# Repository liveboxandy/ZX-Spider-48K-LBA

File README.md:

# ZX-Spider-48K-LBA
ZX Spider 48K Amended by liveboxandy to use 9 Pin MiniDIN and move resistors from under IC's.

Original files from https://github.com/konkotgit/ZX-48-Spider and redrawn in Kicad 10 using the gerbers from konkotgit as an initial layout.
Autorouting along with some manual actions were used for the final pcb layout and gerber generation.

See https://github.com/konkotgit/ZX-48-Spider for more details and any issues that might be seen.

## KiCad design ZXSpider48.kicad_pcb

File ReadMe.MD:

# ZX 48 Spider rework by liveboxandy
## ZX Spectrum 48 clone built on the basis of the ZX Max 48 design.

The board is designed to fit into the standard ZX Spectrum 48k or ZX Spectrum + housing.

## Characteristic:

* ULA based on the CPLD system from the Altera Max7000 family (EPM7128SLC84),
* 48KB RAM,
* AY-3-8910 or AY-3-8912 sound system with stereo output,
* Kempston standard joystick interface,
* RGB video output,
* possibility of using a power supply with any polarity,
* ROM bank switch,
* board fully adapted for through hole mounting

V1.0
* Uses MiniDIN 9 Pin for RGB same as ZX Max 128 & ZX MAx PLusD rather than MinDIN 8.
* Uses same Resistor values for RED/GREEN/BLUE/BRIGHT as ZX Max 128/PlusD/3/2A. 

V1.1
* Joystick can be disabled by removing J18.
* Option to supply +/-12V to edge connector for IF1 Serial support using PS1.

V1.2
* Routed AY3-8910 IOB Bits0-7 to header J18 Pins 1(Bit0)- 8(Bit7).
* Routed AY3-891X IOA Bits0-7 to header J20 Pins 1(Bit0)- 8(Bit7).
* Changed ROM select header to 2 pin rather than 3 pin so added pullup resistor.

V1.3
* Move MiniDIN 9 Pin right by ~2mm so it aligns better with the Video hole in the 14/48K and 48K+
* cases. 

V1.4 
* Correct value of R58 to 470R
* Add jumper J9 to select either 27C256 or 28C256
* Buffer 14Mhz clock more. Use all spare gates
* Label all jumpers

V1.5
* Move position and rotation Q2
* Slight repositioning of J6 (9Pin MiniDIN), R15/16/17/18/73 and J18

V1.6
* Move J6 MiniDIN 9 right by 0.5mm and down by 1mm to better align with 48K+ case.
* Move J11 Ear/Mic right by 0.5mm to better align with 48K+ case.
* Move components below J6 and J5 down to give more space.
* Move Edge Connector left by 0.8mm to centre within 48K+ case cutout.
* Add liveboxandy's Spider 48K V1.6 to silkscreen to try to track different revisions of PCB.

V1.7
* Add R20 for auto RGB selection. can be replaced with wire link if there is a 180R-270R resistor in the cable between miniDIN Pin 2 and Scart Pin 16 or can be left unpopulated if manual selection is used.
* Add R21 and D2 for auto AV 4:3 format. Requires PS1 (+12/-12V Converter) to be fitted. If manual selection, R21 and D2 can be left unpopulated.
* If PS1 is fitted the serial comms on IF1 will still NOT work unless C1 in the IF1 is replaced with a wire link. (The IF1 expects  12VAC which it uses to create -12VDC. The DCDC converter PS1 provides -12VDC but it is blocked by C1 in the IF1.)

V1.8
* Changed STO-92 Inline Transistor footprint to make easier soldering.
* Moved AY chips down to leave gaps between each and also the DIO headers

See https://github.com/konkotgit/ZX-48-Spider Rev 1.1 for original information on the ZX Spider, especially if you have issues.
1) with BRIGHT being low or not visible - Might not, see above.
2) Tape loading issues.

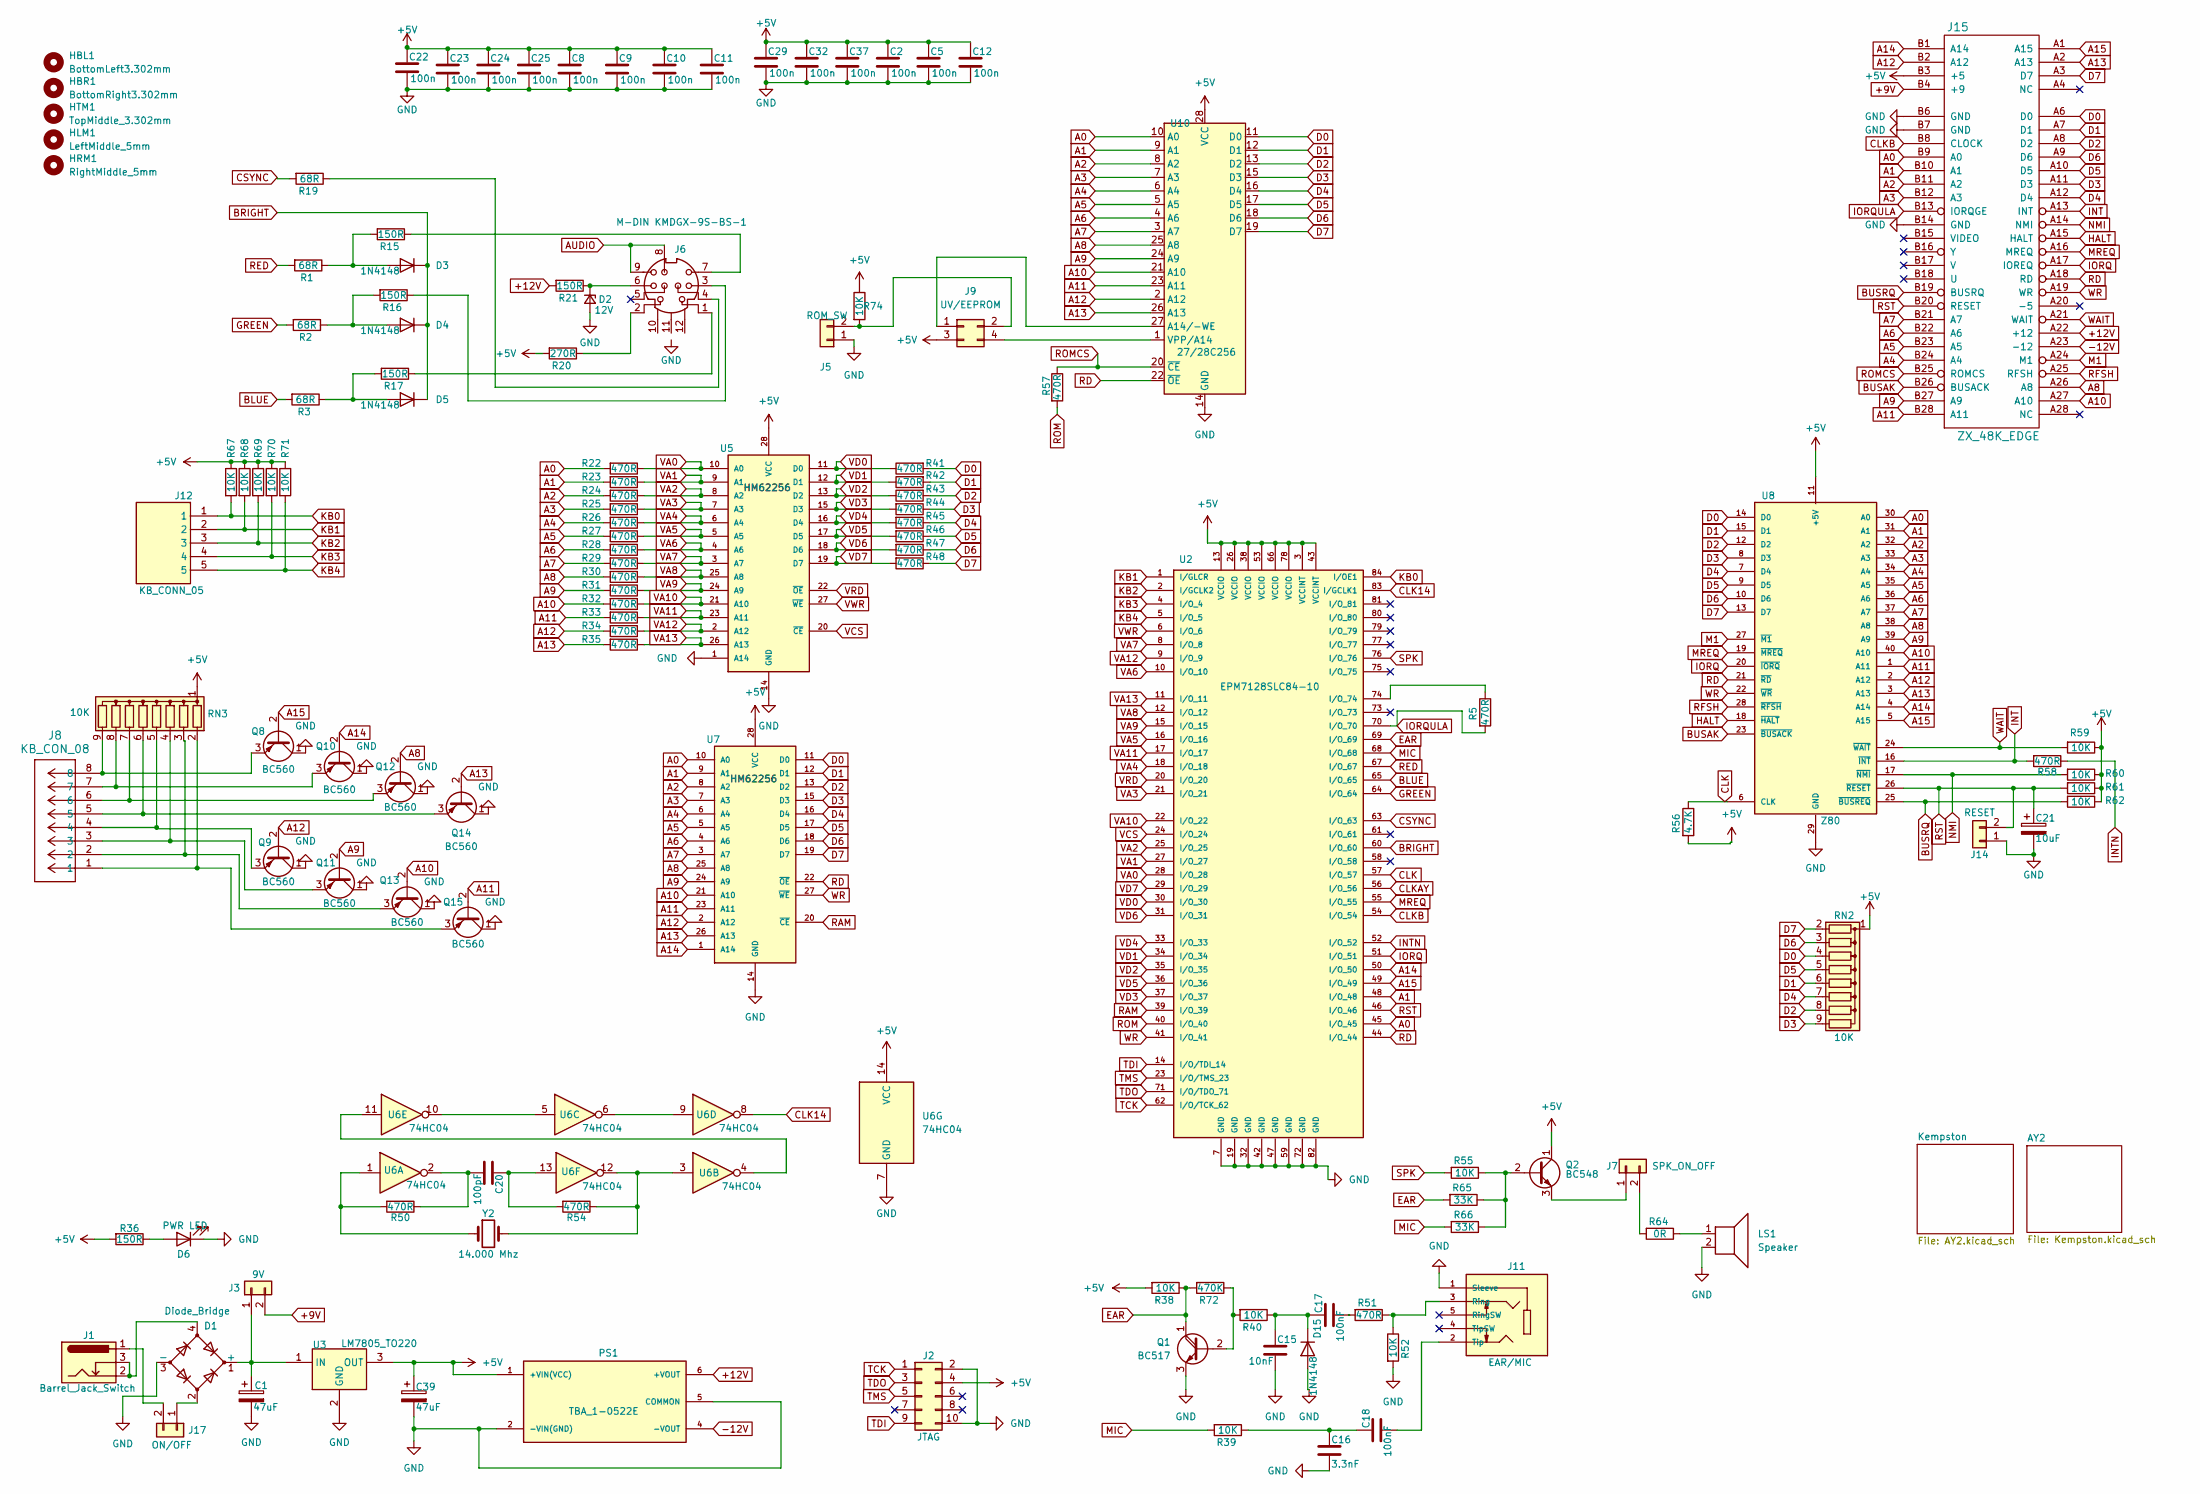
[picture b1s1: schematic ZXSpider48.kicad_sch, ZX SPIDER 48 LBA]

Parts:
C1, C39: 47uF; CP_Radial_D5.0mm_P2.50mm
C2, C5, C8, C9, C10, C11, C12, C22, C23, C24, C25, C29, C32, C37: 100n; C_Disc_D3.0mm_W1.6mm_P2.50mm
C15: 10nF; C_Disc_D3.0mm_W1.6mm_P2.50mm
C16: 3.3nF; C_Disc_D3.0mm_W1.6mm_P2.50mm
C17, C18: 100nF; C_Disc_D3.0mm_W1.6mm_P2.50mm
C20: 100pF; C_Disc_D3.0mm_W1.6mm_P2.50mm
C21: 10uF; CP_Radial_D5.0mm_P2.50mm
D1: Diode_Bridge; Diode_Bridge_Round_D8.9mm
D2: 12V; D_DO-35_SOD27_P7.62mm_Horizontal
D3, D4, D5, D15: 1N4148; D_DO-35_SOD27_P7.62mm_Horizontal
D6: PWR LED; LED_D3.0mm
HBL1: BottomLeft3.302mm; MountingHole_3.3mm Spectrum
HBR1: BottomRight3.302mm; MountingHole_3.3mm Spectrum
HLM1: LeftMiddle_5mm; MountingHole_5mm Spectrum
HRM1: RightMiddle_5mm; MountingHole_5mm Spectrum
HTM1: TopMiddle_3.302mm; MountingHole_3.3mm Spectrum
J1: Barrel_Jack_Switch; BarrelJack_Horizontal
J2: JTAG; PinHeader_2x05_P2.54mm_Vertical
J3: 9V; PinHeader_1x02_P2.54mm_Vertical
J5: ROM_SW; PinHeader_1x02_P2.54mm_Vertical
J6: M-DIN KMDGX-9S-BS-1; KMDGX9SBS1
J7: SPK_ON_OFF; PinHeader_1x02_P2.54mm_Vertical
J8: KB_CON_08; CONN_5-520315-8_TYC
J9: UV/EEPROM; PinHeader_2x02_P2.54mm_Vertical
J11: EAR/MIC; SJ13525NGPI; PARTREV 1.05
J12: KB_CONN_05; CONN_5-520315-5_TYC; Mouser Part Number 571-5-520315-5
J14: RESET; PinHeader_1x02_P2.54mm_Vertical
J15: ZX_48K_EDGE; ZX_BUS_A_TOP
J17: ON/OFF; PinHeader_1x02_P2.54mm_Vertical
LS1: Speaker
PS1: TBA_1-0522E; TBA10522E; Mouser Part Number 495-TBA1-0522E
Q1: BC517; TO-92
Q2: BC548; TO-92_Inline_Wide
Q8, Q9, Q10, Q11, Q12, Q13, Q14, Q15: BC560; TO-92_Inline_Wide
R1, R2, R3, R19: 68R; R_Axial_DIN0204_L3.6mm_D1.6mm_P7.62mm_Horizontal
R5, R22, R23, R24, R25, R26, R27, R28, R29, R30, R31, R32, R33, R34, R35, R41, R42, R43, R44, R45, R46, R47, R48, R50, R51, R54, R57, R58: 470R; R_Axial_DIN0204_L3.6mm_D1.6mm_P7.62mm_Horizontal
R15, R16, R17, R36: 150R; R_Axial_DIN0204_L3.6mm_D1.6mm_P7.62mm_Horizontal
R20: 270R; R_Axial_DIN0204_L3.6mm_D1.6mm_P7.62mm_Horizontal
R21: 150R; R_Axial_DIN0207_L6.3mm_D2.5mm_P15.24mm_Horizontal
R38, R39, R40, R52, R55, R59, R60, R61, R62, R67, R68, R69, R70, R71, R74: 10K; R_Axial_DIN0204_L3.6mm_D1.6mm_P7.62mm_Horizontal
R56: 4.7K; R_Axial_DIN0204_L3.6mm_D1.6mm_P7.62mm_Horizontal
R64: 0R; R_Axial_DIN0204_L3.6mm_D1.6mm_P7.62mm_Horizontal
R65, R66: 33K; R_Axial_DIN0204_L3.6mm_D1.6mm_P7.62mm_Horizontal
R72: 470K; R_Axial_DIN0204_L3.6mm_D1.6mm_P7.62mm_Horizontal
RN2, RN3: 10K; R_Array_SIP9
U2: EPM7128SLC84-10; PLCC-84_THT-Socket; PARTREV 6.7
U3: LM7805_TO220; TO-220-3_Horizontal_TabDown; Mouser Part Number 926-LM7805CT/NOPB
U5, U7: HM62256; DIP-28_W15.24mm_Socket
U6: 74HC04; DIP-14_W7.62mm_Socket
U8: Z80; DIP-40_W15.24mm_Socket
U10: 27/28C256; DIP-28_W15.24mm_Socket
Y2: 14.000 Mhz; Crystal_HC49-4H_Vertical

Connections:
+5V: C2.1, C5.1, C8.1, C9.1, C10.1, C11.1, C12.1, C22.1, C23.1, C24.1, C25.1, C29.1, C32.1, C37.1, C39.1, J2.4, J9.3, J15.B3 (+5), PS1.1 (+VIN(VCC)), Q2.1 (C), R20.2, R36.2, R38.2, R56.2, R59.1, R60.1, R61.1, R62.1, R67.1, R68.1, R69.1, R70.1, R71.1, R74.1, RN2.1 (common), RN3.1 (common), U2.3 (VCCINT), U2.13 (VCCIO), U2.26 (VCCIO), U2.38 (VCCIO), U2.43 (VCCINT), U2.53 (VCCIO), U2.66 (VCCIO), U2.78 (VCCIO), U3.3 (OUT), U5.28 (VCC), U6.14 (VCC), U7.28 (VCC), U8.11 (+5V), U10.28 (VCC); also elsewhere on the board
+9V: J3.2, J15.B4 (+9)
+12V: J15.A22 (+12), PS1.6 (+VOUT), R21.2
-12V: J15.A23 (-12), PS1.4 (-VOUT)
A0: J15.B9 (A0), R22.2, U2.45 (I/O_45), U7.10 (A0), U8.30 (A0), U10.10 (A0)
A1: J15.B10 (A1), R23.2, U2.48 (I/O_48), U7.9 (A1), U8.31 (A1), U10.9 (A1); also elsewhere on the board
A2: J15.B11 (A2), R24.2, U7.8 (A2), U8.32 (A2), U10.8 (A2)
A3: J15.B12 (A3), R25.2, U7.7 (A3), U8.33 (A3), U10.7 (A3)
A4: J15.B24 (A4), R26.2, U7.6 (A4), U8.34 (A4), U10.6 (A4)
A5: J15.B23 (A5), R27.2, U7.5 (A5), U8.35 (A5), U10.5 (A5); also elsewhere on the board
A6: J15.B22 (A6), R28.2, U7.4 (A6), U8.36 (A6), U10.4 (A6)
A7: J15.B21 (A7), R29.2, U7.3 (A7), U8.37 (A7), U10.3 (A7)
A8: J15.A26 (A8), Q12.2 (B), R30.2, U7.25 (A8), U8.38 (A8), U10.25 (A8)
A9: J15.B27 (A9), Q11.2 (B), R31.2, U7.24 (A9), U8.39 (A9), U10.24 (A9)
A10: J15.A27 (A10), Q13.2 (B), R32.2, U7.21 (A10), U8.40 (A10), U10.21 (A10)
A11: J15.B28 (A11), Q15.2 (B), R33.2, U7.23 (A11), U8.1 (A11), U10.23 (A11)
A12: J15.B2 (A12), Q9.2 (B), R34.2, U7.2 (A12), U8.2 (A12), U10.2 (A12)
A13: J15.A2 (A13), Q14.2 (B), R35.2, U7.26 (A13), U8.3 (A13), U10.26 (A13)
A14: J15.B1 (A14), Q10.2 (B), U2.50 (I/O_50), U7.1 (A14), U8.4 (A14); also elsewhere on the board
A15: J15.A1 (A15), Q8.2 (B), U2.49 (I/O_49), U8.5 (A15); also elsewhere on the board
AUDIO: J6.8, J6.9; also elsewhere on the board
BLUE: R3.2, U2.65 (I/O_65)
BRIGHT: D3.1 (K), D4.1 (K), D5.1 (K), U2.60 (I/O_60)
BUSAK: J15.B26 (BUSACK), U8.23 (~BUSACK)
BUSRQ: J15.B19 (BUSRQ), R62.2, U8.25 (~BUSREQ)
CLK: R56.1, U2.57 (I/O_57), U8.6 (CLK)
CLK14: U2.83 (I/GCLK1), U6.8
CLKAY: U2.56 (I/O_56); also elsewhere on the board
CLKB: J15.B8 (CLOCK), U2.54 (I/O_54)
CSYNC: R19.2, U2.63 (I/O_63)
D0: J15.A6 (D0), R41.2, RN2.4 (R3), U7.11 (D0), U8.14 (D0), U10.11 (D0); also elsewhere on the board
D1: J15.A7 (D1), R42.2, RN2.6 (R5), U7.12 (D1), U8.15 (D1), U10.12 (D1); also elsewhere on the board
D2: J15.A8 (D2), R43.2, RN2.8 (R7), U7.13 (D2), U8.12 (D2), U10.13 (D2); also elsewhere on the board
D3: J15.A11 (D3), R44.1, RN2.9 (R8), U7.15 (D3), U8.8 (D3), U10.15 (D3); also elsewhere on the board
D4: J15.A12 (D4), R45.1, RN2.7 (R6), U7.16 (D4), U8.7 (D4), U10.16 (D4); also elsewhere on the board
D5: J15.A10 (D5), R46.1, RN2.5 (R4), U7.17 (D5), U8.9 (D5), U10.17 (D5); also elsewhere on the board
D6: J15.A9 (D6), R47.1, RN2.3 (R2), U7.18 (D6), U8.10 (D6), U10.18 (D6); also elsewhere on the board
D7: J15.A3 (D7), R48.1, RN2.2 (R1), U7.19 (D7), U8.13 (D7), U10.19 (D7); also elsewhere on the board
EAR: Q1.1 (C), R38.1, R65.2, R72.2, U2.69 (I/O_69); also elsewhere on the board
GND: C1.2, C2.2, C5.2, C8.2, C9.2, C10.2, C11.2, C12.2, C15.2, C16.2, C21.2, C22.2, C23.2, C24.2, C25.2, C29.2, C32.2, C37.2, C39.2, D1.3 (-), D2.2 (A), D6.1 (K), D15.2 (A), J2.2, J2.10, J5.1, J11.1 (Sleeve), J14.1, J15.B6 (GND), J15.B7 (GND), J15.B14 (GND), LS1.2, PS1.2 (-VIN(GND)), PS1.5 (COMMON), Q1.3 (E), Q8.1 (C), Q9.1 (C), Q10.1 (C), Q11.1 (C), Q12.1 (C), Q13.1 (C), Q14.1 (C), Q15.1 (C), R52.2, U2.7 (GND), U2.19 (GND), U2.32 (GND), U2.42 (GND), U2.47 (GND), U2.59 (GND), U2.72 (GND), U2.82 (GND), U3.2 (GND), U5.1 (A14), U5.14 (GND), U6.7 (GND), U7.14 (GND), U8.29 (GND), U10.14 (GND); also elsewhere on the board
GREEN: R2.2, U2.64 (I/O_64)
HALT: J15.A15 (HALT), U8.18 (~HALT)
INT: J15.A13 (INT), R58.2, U8.16 (~INT)
INTN: R58.1, U2.52 (I/O_52)
IORQ: J15.A17 (IOREQ), U2.51 (I/O_51), U8.20 (~IORQ); also elsewhere on the board
IORQULA: J15.B13 (IORQGE), R5.2, U2.70 (I/O_70)
KB0: J12.1, R67.2, U2.84 (I/OE1)
KB1: J12.2, R68.2, U2.1 (I/GLCR)
KB2: J12.3, R69.2, U2.2 (I/GCLK2)
KB3: J12.4, R70.2, U2.4 (I/O_4)
KB4: J12.5, R71.2, U2.5 (I/O_5)
M1: J15.A24 (M1), U8.27 (~M1)
MIC: R39.2, R66.2, U2.68 (I/O_68); also elsewhere on the board
MREQ: J15.A16 (MREQ), U2.55 (I/O_55), U8.19 (~MREQ)
NMI: J15.A14 (NMI), R60.2, U8.17 (~NMI)
unnamed: C16.1, C18.1, R39.1
unnamed: C17.2, R51.2
unnamed: C20.1, R50.1, U6.2
unnamed: C20.2, R54.2, U6.13
unnamed: C1.1, D1.1 (+), J3.1, U3.1 (IN)
unnamed: D1.4, J1.2, J1.3
unnamed: D2.1 (K), J6.6, R21.1
unnamed: D3.2 (A), R1.1, R15.2
unnamed: D4.2 (A), R2.1, R16.2
unnamed: D5.2 (A), R3.1, R17.2
unnamed: D6.2 (A), R36.1
unnamed: C15.1, C17.1, D15.1 (K), R40.1
unnamed: J5.2, J9.2, R74.2
unnamed: J6.1, R17.1
unnamed: J6.2, R20.1
unnamed: J6.3, R16.1
unnamed: J6.4, R19.1
unnamed: J6.7, R15.1
unnamed: J7.1, Q2.3 (E)
unnamed: J7.2, R64.2
unnamed: J9.1, U10.27 (A14/-WE)
unnamed: J9.4, U10.1 (VPP/A14)
unnamed: J11.3 (Ring), R51.1, R52.1
unnamed: C18.2, J11.2 (Tip)
unnamed: D1.2, J17.1
unnamed: J1.1, J17.2
unnamed: LS1.1, R64.1
unnamed: Q1.2 (B), R40.2, R72.1
unnamed: Q2.2 (B), R55.1, R65.1, R66.1
unnamed: J8.8, Q8.3 (E), RN3.9 (R8)
unnamed: J8.4, Q9.3 (E), RN3.5 (R4)
unnamed: J8.7, Q10.3 (E), RN3.8 (R7)
unnamed: J8.3, Q11.3 (E), RN3.4 (R3)
unnamed: J8.6, Q12.3 (E), RN3.7 (R6)
unnamed: J8.2, Q13.3 (E), RN3.3 (R2)
unnamed: J8.5, Q14.3 (E), RN3.6 (R5)
unnamed: J8.1, Q15.3 (E), RN3.2 (R1)
unnamed: R50.2, U6.1, Y2.1
unnamed: R54.1, U6.3, U6.12, Y2.2
unnamed: R5.1, U2.74 (I/O_74)
unnamed: U6.6, U6.9
unnamed: U6.5, U6.10
unnamed: U6.4, U6.11
RAM: U2.39 (I/O_39), U7.20 (~CE)
RD: J15.A18 (RD), U2.44 (I/O_44), U7.22 (~OE), U8.21 (~RD), U10.22 (~OE); also elsewhere on the board
RED: R1.2, U2.67 (I/O_67)
RFSH: J15.A25 (RFSH), U8.28 (~RFSH)
ROM: R57.2, U2.40 (I/O_40)
ROMCS: J15.B25 (ROMCS), R57.1, U10.20 (~CE)
RST: C21.1, J14.2, J15.B20 (RESET), R61.2, U2.46 (I/O_46), U8.26 (~RESET); also elsewhere on the board
SPK: R55.2, U2.76 (I/O_76); also elsewhere on the board
TCK: J2.1, U2.62 (I/O/TCK_62)
TDI: J2.9, U2.14 (I/O/TDI_14)
TDO: J2.3, U2.71 (I/O/TDO_71)
TMS: J2.5, U2.23 (I/O/TMS_23)
VA0: R22.1, U2.28 (I/O_28), U5.10 (A0)
VA1: R23.1, U2.27 (I/O_27), U5.9 (A1)
VA2: R24.1, U2.25 (I/O_25), U5.8 (A2)
VA3: R25.1, U2.21 (I/O_21), U5.7 (A3)
VA4: R26.1, U2.18 (I/O_18), U5.6 (A4)
VA5: R27.1, U2.16 (I/O_16), U5.5 (A5)
VA6: R28.1, U2.10 (I/O_10), U5.4 (A6)
VA7: R29.1, U2.8 (I/O_8), U5.3 (A7)
VA8: R30.1, U2.12 (I/O_12), U5.25 (A8)
VA9: R31.1, U2.15 (I/O_15), U5.24 (A9)
VA10: R32.1, U2.22 (I/O_22), U5.21 (A10)
VA11: R33.1, U2.17 (I/O_17), U5.23 (A11)
VA12: R34.1, U2.9 (I/O_9), U5.2 (A12)
VA13: R35.1, U2.11 (I/O_11), U5.26 (A13)
VCS: U2.24 (I/O_24), U5.20 (~CE)
VD0: R41.1, U2.30 (I/O_30), U5.11 (D0)
VD1: R42.1, U2.34 (I/O_34), U5.12 (D1)
VD2: R43.1, U2.35 (I/O_35), U5.13 (D2)
VD3: R44.2, U2.37 (I/O_37), U5.15 (D3)
VD4: R45.2, U2.33 (I/O_33), U5.16 (D4)
VD5: R46.2, U2.36 (I/O_36), U5.17 (D5)
VD6: R47.2, U2.31 (I/O_31), U5.18 (D6)
VD7: R48.2, U2.29 (I/O_29), U5.19 (D7)
VRD: U2.20 (I/O_20), U5.22 (~OE)
VWR: U2.6 (I/O_6), U5.27 (~WE)
WAIT: J15.A21 (WAIT), R59.2, U8.24 (~WAIT)
WR: J15.A19 (WR), U2.41 (I/O_41), U7.27 (~WE), U8.22 (~WR); also elsewhere on the board

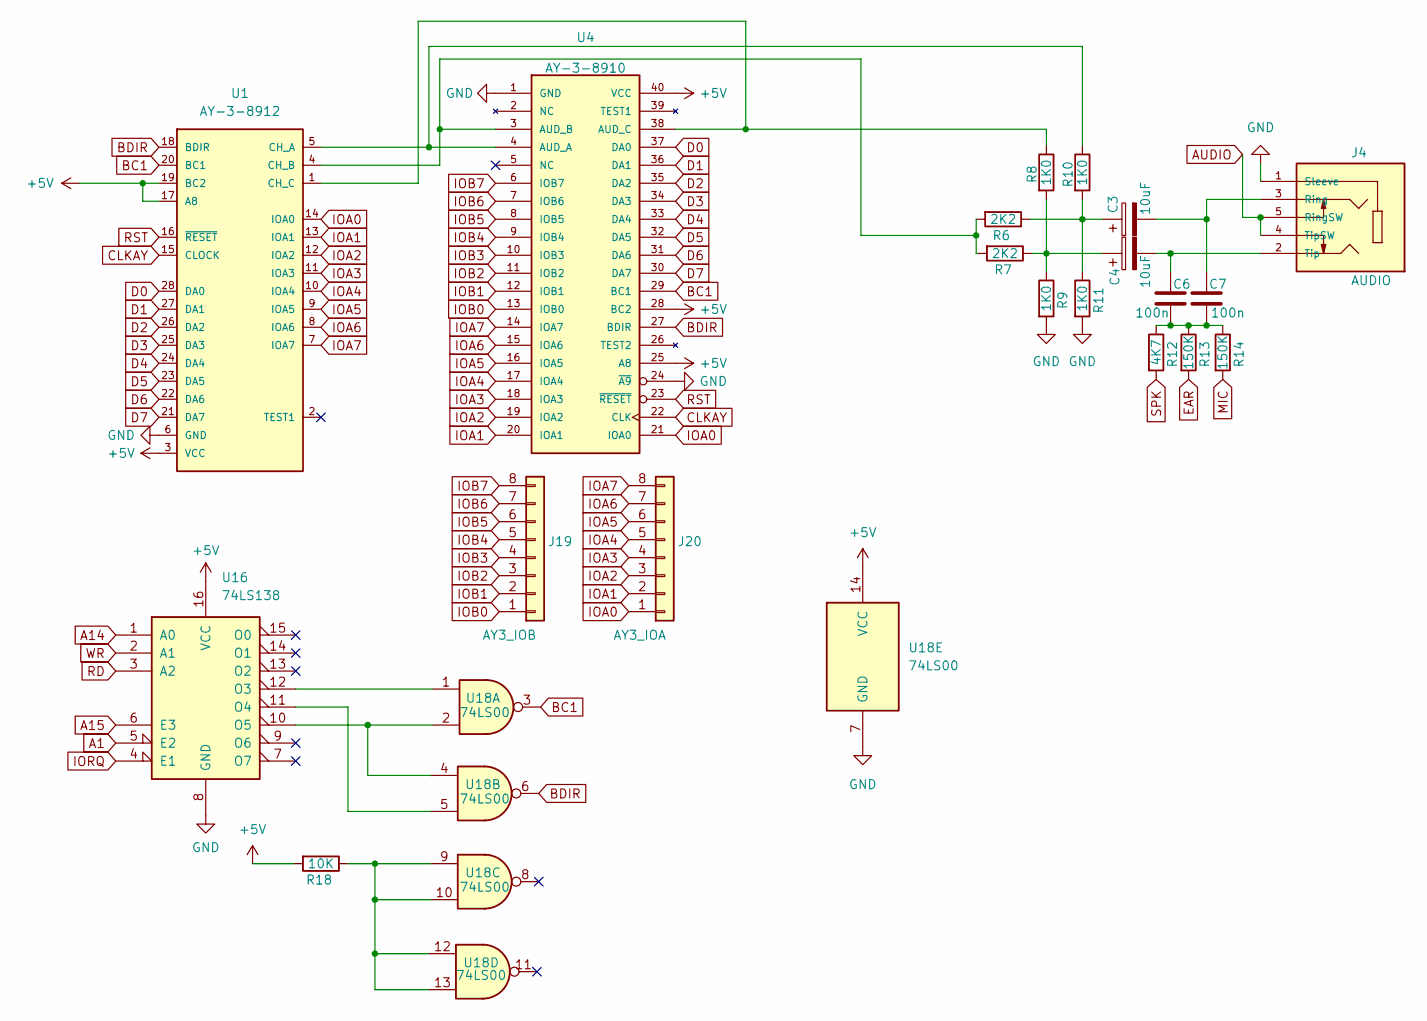
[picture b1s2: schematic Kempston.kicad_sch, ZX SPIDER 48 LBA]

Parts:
C3, C4: 10uF; CP_Radial_D5.0mm_P2.50mm
C6, C7: 100n; C_Disc_D3.0mm_W1.6mm_P2.50mm
J4: AUDIO; SJ13525NGPI; PARTREV 1.05; Mouser Part Number 490-SJ1-3525NG-PI
J19: AY3_IOB; PinHeader_1x08_P2.54mm_Vertical
J20: AY3_IOA; PinHeader_1x08_P2.54mm_Vertical
R6, R7: 2K2; R_Axial_DIN0204_L3.6mm_D1.6mm_P7.62mm_Horizontal
R8, R9, R10, R11: 1K0; R_Axial_DIN0204_L3.6mm_D1.6mm_P7.62mm_Horizontal
R12: 4K7; R_Axial_DIN0204_L3.6mm_D1.6mm_P7.62mm_Horizontal
R13, R14: 150K; R_Axial_DIN0204_L3.6mm_D1.6mm_P7.62mm_Horizontal
R18: 10K; R_Axial_DIN0204_L3.6mm_D1.6mm_P7.62mm_Horizontal
U1: AY-3-8912; DIP-28_W15.24mm_Socket
U4: AY-3-8910; DIP-40_W15.24mm_Socket
U16: 74LS138; DIP-16_W7.62mm_Socket
U18: 74LS00; DIP-14_W7.62mm_Socket

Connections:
+5V: R18.2, U1.3 (VCC), U1.17 (A8), U1.19 (BC2), U4.25 (A8), U4.28 (BC2), U4.40 (VCC), U16.16 (VCC), U18.14 (VCC); also elsewhere on the board
A1: U16.5 (E2); also elsewhere on the board
A14: U16.1 (A0); also elsewhere on the board
A15: U16.6 (E3); also elsewhere on the board
AUDIO: J4.4 (TipSW), J4.5 (RingSW); also elsewhere on the board
BC1: U1.20 (BC1), U4.29 (BC1), U18.3
BDIR: U1.18 (BDIR), U4.27 (BDIR), U18.6
CLKAY: U1.15 (CLOCK), U4.22 (CLK); also elsewhere on the board
D0: U1.28 (DA0), U4.37 (DA0); also elsewhere on the board
D1: U1.27 (DA1), U4.36 (DA1); also elsewhere on the board
D2: U1.26 (DA2), U4.35 (DA2); also elsewhere on the board
D3: U1.25 (DA3), U4.34 (DA3); also elsewhere on the board
D4: U1.24 (DA4), U4.33 (DA4); also elsewhere on the board
D5: U1.23 (DA5), U4.32 (DA5); also elsewhere on the board
D6: U1.22 (DA6), U4.31 (DA6); also elsewhere on the board
D7: U1.21 (DA7), U4.30 (DA7); also elsewhere on the board
EAR: R13.2; also elsewhere on the board
GND: J4.1 (Sleeve), R9.2, R11.2, U1.6 (GND), U4.1 (GND), U4.24 (~A9), U16.8 (GND), U18.7 (GND); also elsewhere on the board
IOA0: J20.1, U1.14 (IOA0), U4.21 (IOA0)
IOA1: J20.2, U1.13 (IOA1), U4.20 (IOA1)
IOA2: J20.3, U1.12 (IOA2), U4.19 (IOA2)
IOA3: J20.4, U1.11 (IOA3), U4.18 (IOA3)
IOA4: J20.5, U1.10 (IOA4), U4.17 (IOA4)
IOA5: J20.6, U1.9 (IOA5), U4.16 (IOA5)
IOA6: J20.7, U1.8 (IOA6), U4.15 (IOA6)
IOA7: J20.8, U1.7 (IOA7), U4.14 (IOA7)
IOB0: J19.1, U4.13 (IOB0)
IOB1: J19.2, U4.12 (IOB1)
IOB2: J19.3, U4.11 (IOB2)
IOB3: J19.4, U4.10 (IOB3)
IOB4: J19.5, U4.9 (IOB4)
IOB5: J19.6, U4.8 (IOB5)
IOB6: J19.7, U4.7 (IOB6)
IOB7: J19.8, U4.6 (IOB7)
IORQ: U16.4 (E1); also elsewhere on the board
MIC: R14.2; also elsewhere on the board
unnamed: C3.1, R6.1, R10.2, R11.1
unnamed: C4.1, R7.1, R8.2, R9.1
unnamed: C6.2, C7.2, R12.1, R13.1, R14.1
unnamed: C3.2, C7.1, J4.3 (Ring)
unnamed: C4.2, C6.1, J4.2 (Tip)
unnamed: R18.1, U18.9, U18.10, U18.12, U18.13
unnamed: R10.1, U1.5 (CH_A), U4.4 (AUD_A)
unnamed: R6.2, R7.2, U1.4 (CH_B), U4.3 (AUD_B)
unnamed: R8.1, U1.1 (CH_C), U4.38 (AUD_C)
unnamed: U16.12 (O3), U18.1
unnamed: U16.11 (O4), U18.5
unnamed: U16.10 (O5), U18.2, U18.4
RD: U16.3 (A2); also elsewhere on the board
RST: U1.16 (~RESET), U4.23 (~RESET); also elsewhere on the board
SPK: R12.2; also elsewhere on the board
WR: U16.2 (A1); also elsewhere on the board

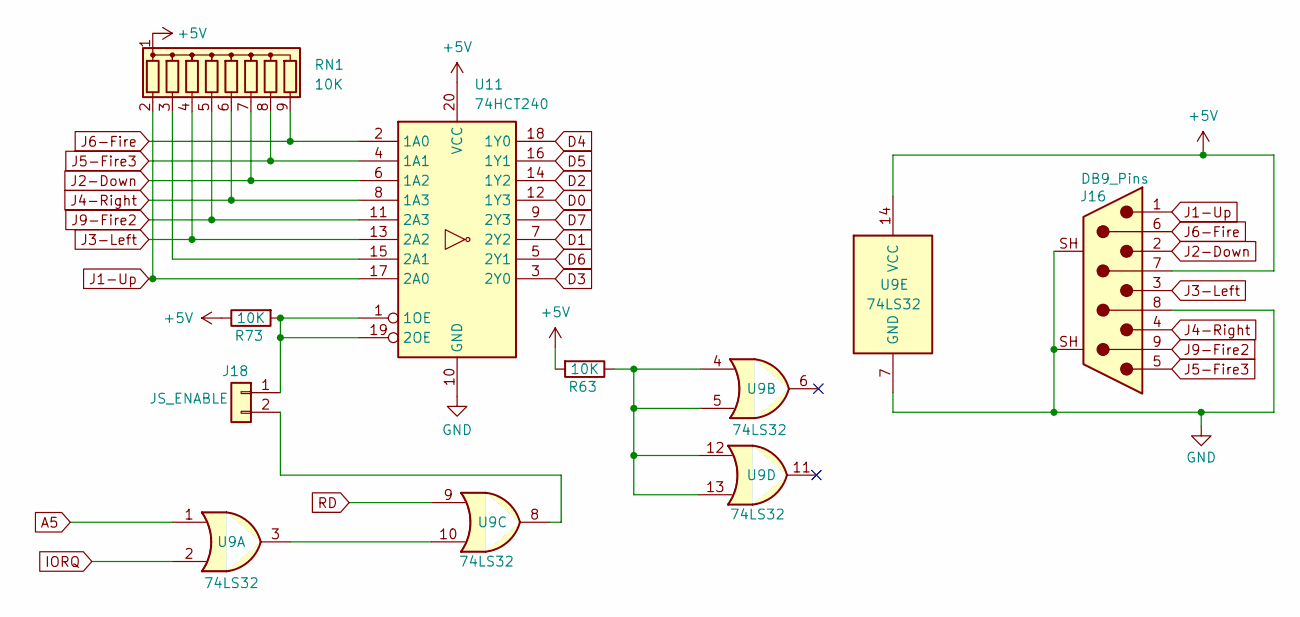
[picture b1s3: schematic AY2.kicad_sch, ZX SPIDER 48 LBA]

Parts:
J16: DB9_Pins; DSUB-9_Pins_Horizontal_P2.77x2.84mm_EdgePinOffset9.90mm_Hou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
J18: JS_ENABLE; PinHeader_1x02_P2.54mm_Vertical
R63, R73: 10K; R_Axial_DIN0204_L3.6mm_D1.6mm_P7.62mm_Horizontal
RN1: 10K; R_Array_SIP9
U9: 74LS32; DIP-14_W7.62mm_Socket
U11: 74HCT240; DIP-20_W7.62mm_Socket

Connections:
+5V: J16.7, R63.2, R73.1, RN1.1 (common), U9.14 (VCC), U11.20 (VCC); also elsewhere on the board
A5: U9.1; also elsewhere on the board
D0: U11.12 (1Y3); also elsewhere on the board
D1: U11.7 (2Y2); also elsewhere on the board
D2: U11.14 (1Y2); also elsewhere on the board
D3: U11.3 (2Y0); also elsewhere on the board
D4: U11.18 (1Y0); also elsewhere on the board
D5: U11.16 (1Y1); also elsewhere on the board
D6: U11.5 (2Y1); also elsewhere on the board
D7: U11.9 (2Y3); also elsewhere on the board
GND: J16.8, J16.SH (Shell), U9.7 (GND), U11.10 (GND); also elsewhere on the board
IORQ: U9.2; also elsewhere on the board
J1-Up: J16.1, RN1.2 (R1), U11.17 (2A0)
J2-Down: J16.2, RN1.7 (R6), U11.6 (1A2)
J3-Left: J16.3, RN1.4 (R3), U11.13 (2A2)
J4-Right: J16.4, RN1.6 (R5), U11.8 (1A3)
J5-Fire3: J16.5, RN1.8 (R7), U11.4 (1A1)
J6-Fire: J16.6, RN1.9 (R8), U11.2 (1A0)
J9-Fire2: J16.9, RN1.5 (R4), U11.11 (2A3)
unnamed: J18.1, R73.2, U11.1 (1OE), U11.19 (2OE)
unnamed: J18.2, U9.8
unnamed: R63.1, U9.4, U9.5, U9.12, U9.13
unnamed: RN1.3 (R2), U11.15 (2A1)
unnamed: U9.3, U9.10
RD: U9.9; also elsewhere on the board

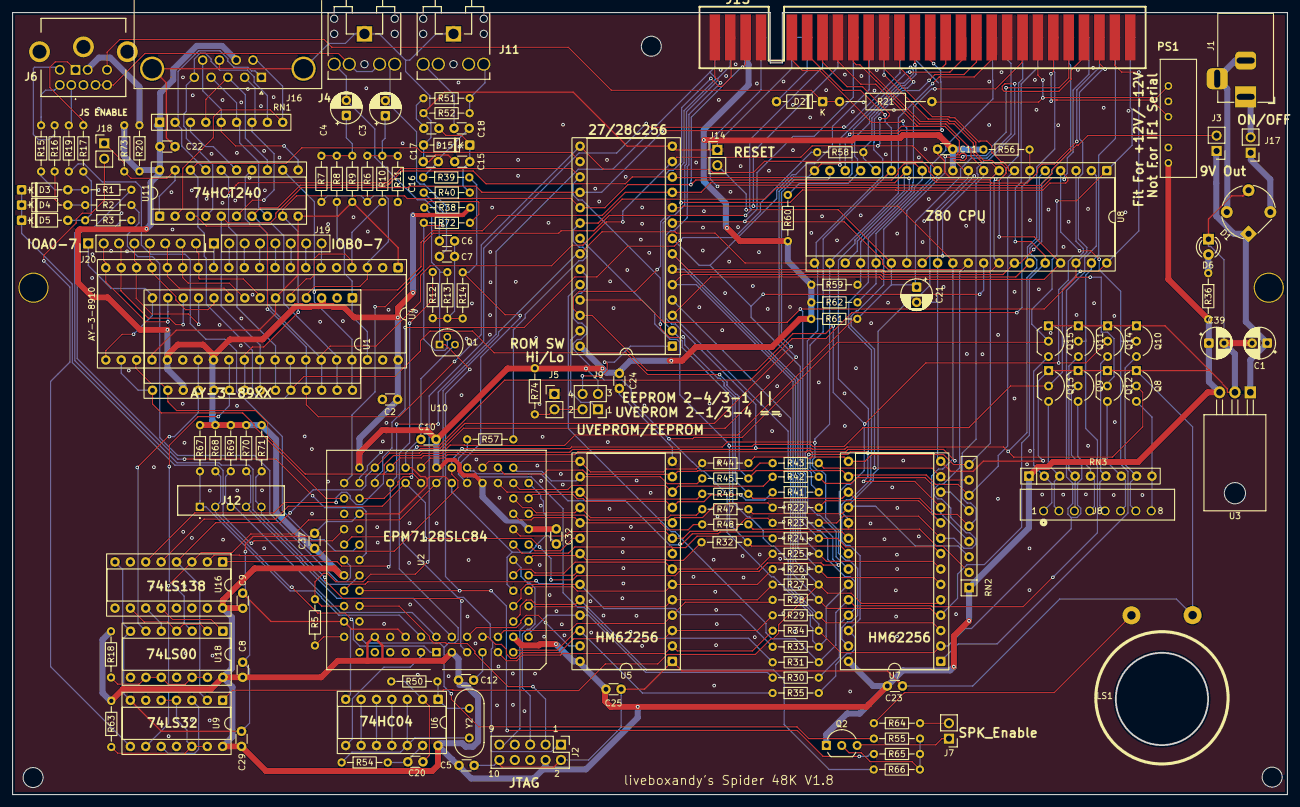
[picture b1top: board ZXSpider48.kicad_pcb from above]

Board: 2 copper layers, 210.3 x 129.0 mm, 155 parts (0 on the bottom side), 179 nets.

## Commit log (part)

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2026-06-21 Update README with project details and sources
    Added additional information about the project and its origins.
2026-06-21 Initial Release of Files
2026-06-21 Initial upload of 3d step files
2026-06-24 Add files via upload
    Added optional +/-12V for IF2 Serial support. Only fit if required.
    Added jumper J18 to enable/disable Joystick interface ( fitted to enable, remove to disable).
2026-06-25 Added header for AY3-8910 IOB (J18) and moved position of U1 and U4
    * Routed AY3-8910 IOB Bits0-7 to header J18 Pins 1(Bit0)- 8(Bit7)
    * AY3-8910 IOA Bits 0-7 can be picked from U1 pins 7(Bit7)-14(Bit0)
    * AY3-8912 IOA Bits 1-7 can be picked from U4 Pins 14(Bit7)-20(Bit1)
    * AY3-8912 IOA Bit0 can be picked from J20
2026-06-26 Add files via upload
    Changed ROM select to 2 pin rather than 3 pin header
